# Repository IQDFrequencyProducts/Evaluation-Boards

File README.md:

# Evaluation-Boards
IQD frequency product evaluation boards. Includes schematics and PCB Files.

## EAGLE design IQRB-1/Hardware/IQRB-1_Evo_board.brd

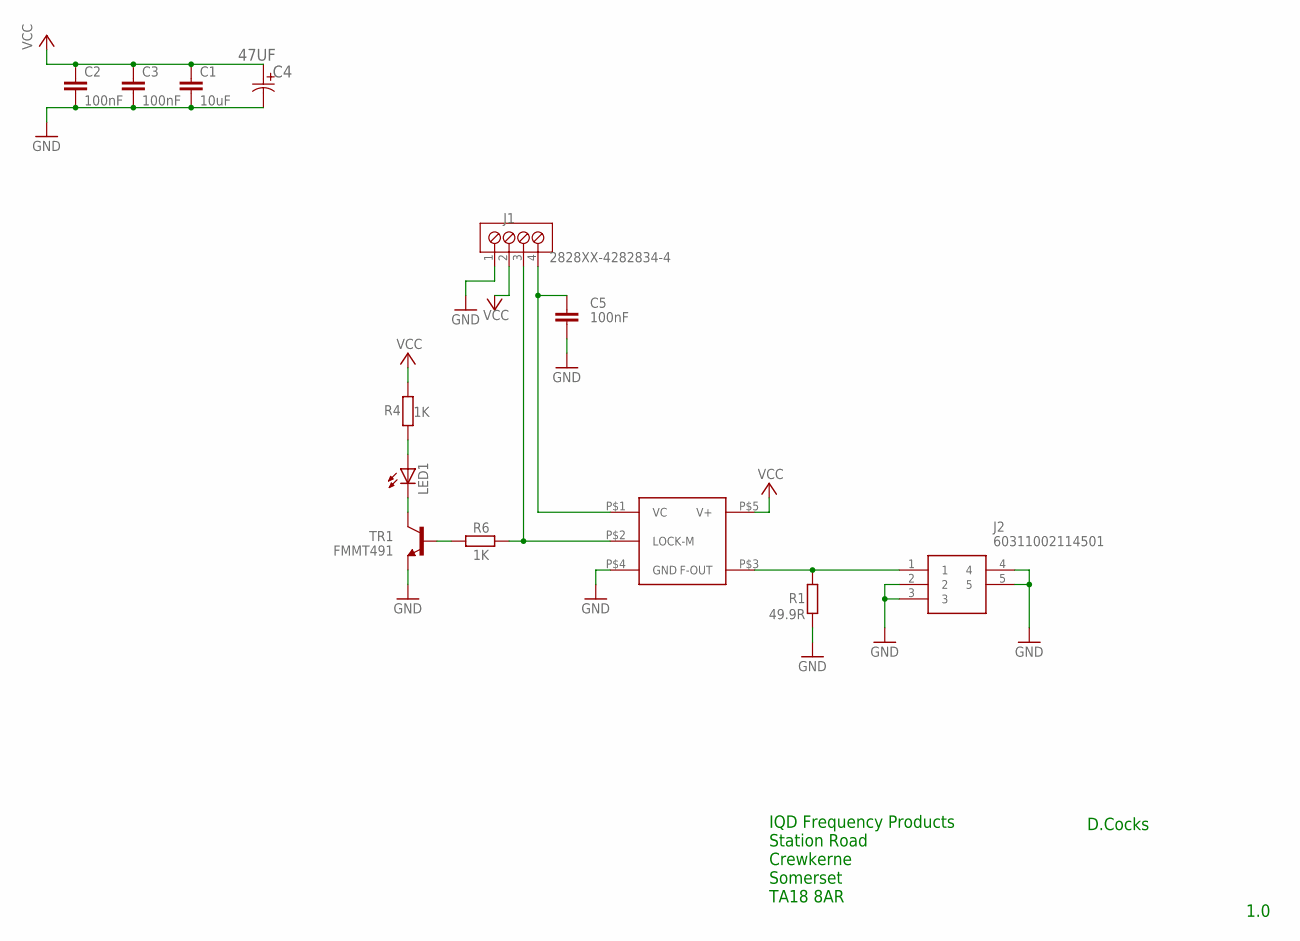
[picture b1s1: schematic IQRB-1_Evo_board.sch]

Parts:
C1: 10uF; C0805
C2, C3, C5: 100nF; C0805
C4: 47UF; CAPAE530X610N
J1: 2828XX-4282834-4; TERMBLK_254-4N
J2: 60311002114501; 60312002114503
LED1: LEDCHIP-LED0805; CHIP-LED0805
R1: 49.9R; M1206
R4, R6: 1K; M0805
TR1: FMMT491; SOT23-BEC
U$1: RB1-DEVRUBID; RB1-PACK

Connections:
GND: C1.2, C2.2, C3.2, C4.2, C5.2, J1.1, J2.2, J2.3, J2.4, J2.5, R1.1, TR1.E, U$1.P$4 (GND)
unnamed: R6.1, TR1.B
unnamed: J2.1, R1.2, U$1.P$3 (F-OUT)
unnamed: LED1.C, TR1.C
unnamed: LED1.A, R4.1
unnamed: J1.3, R6.2, U$1.P$2 (LOCK-M)
unnamed: C5.1, J1.4, U$1.P$1 (VC)
VCC: C1.1, C2.1, C3.1, C4.1, J1.2, R4.2, U$1.P$5 (V+)

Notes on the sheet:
D.Cocks
IQD Frequency Products Station Road Crewkerne Somerset TA18 8AR
1.0

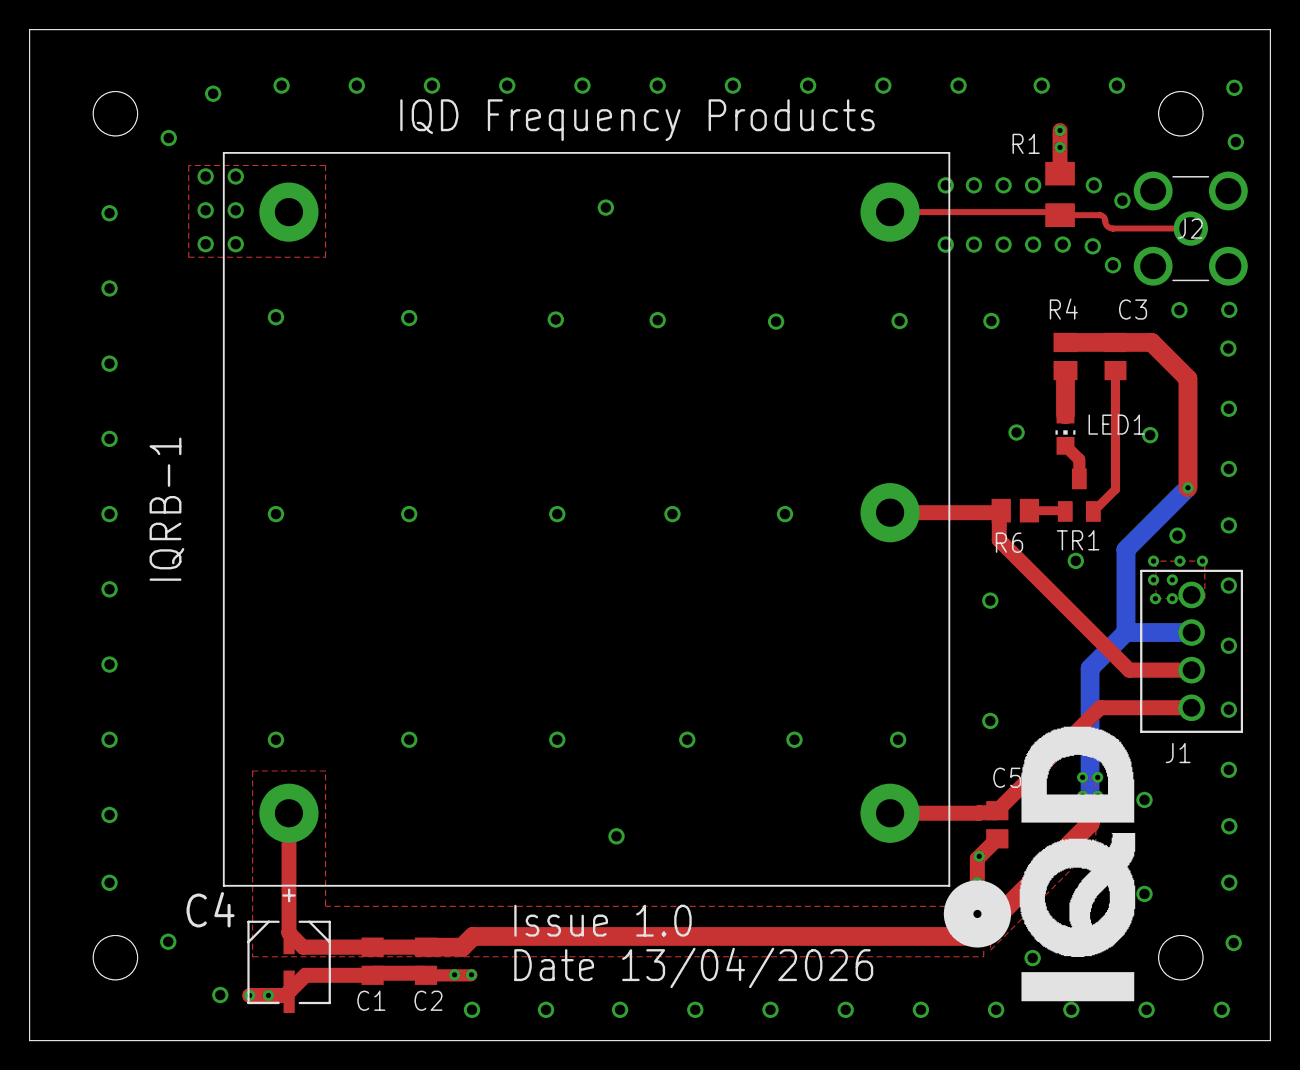
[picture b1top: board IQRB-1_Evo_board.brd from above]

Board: 4 copper layers, 83.8 x 68.3 mm, 13 parts (0 on the bottom side), 8 nets.
